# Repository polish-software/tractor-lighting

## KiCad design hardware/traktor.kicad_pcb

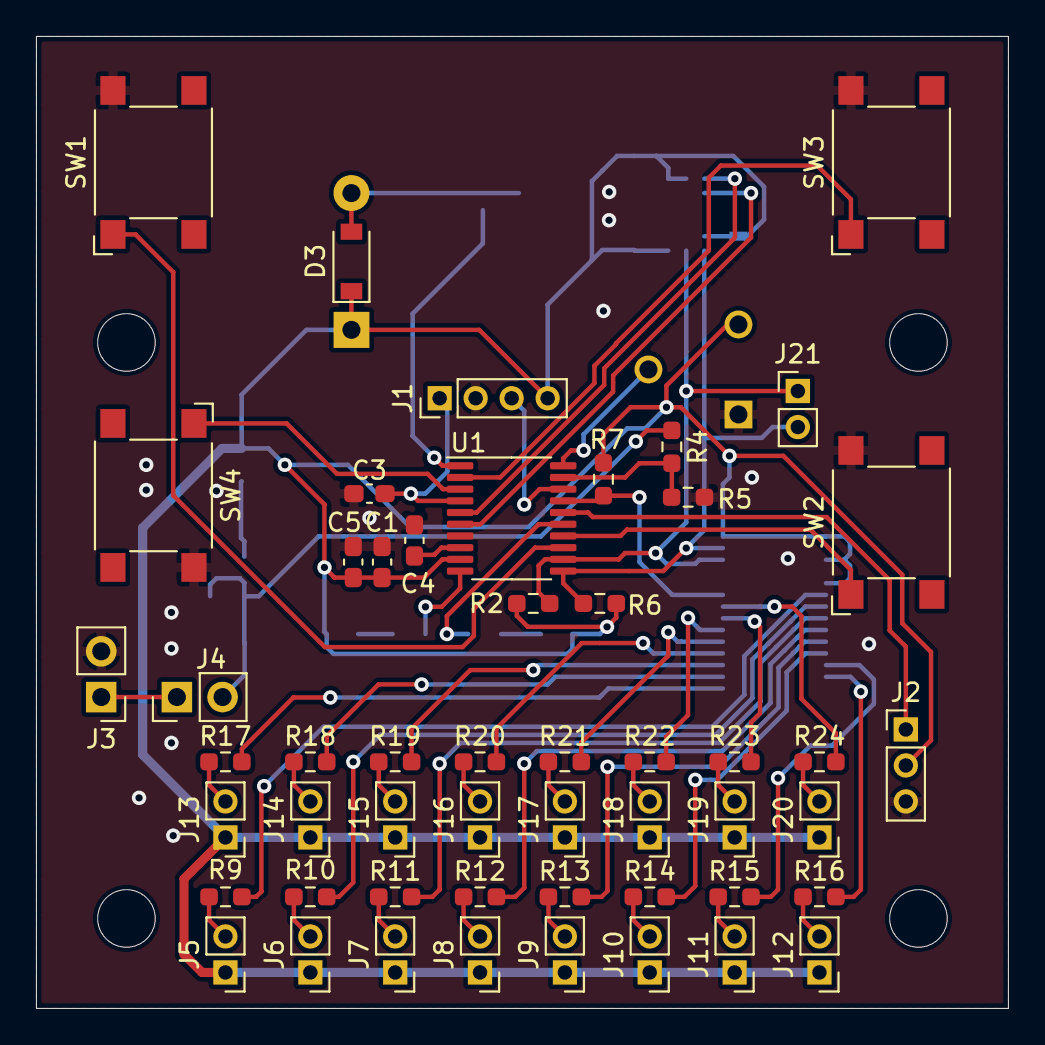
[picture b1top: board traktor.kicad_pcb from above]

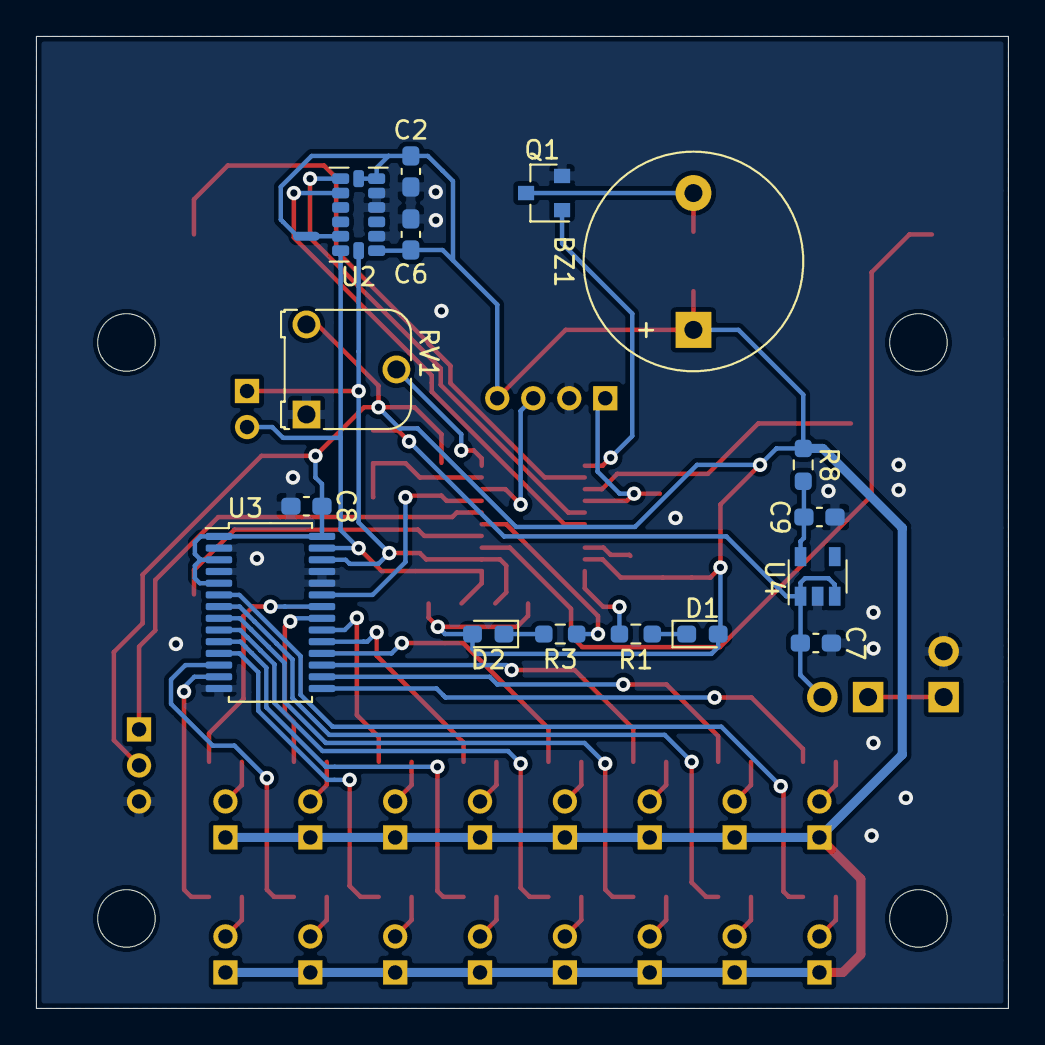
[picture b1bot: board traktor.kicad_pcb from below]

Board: 2 copper layers, 54.0 x 54.0 mm, 69 parts (17 on the bottom side), 59 nets.

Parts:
BZ1: Buzzer; Buzzer_12x9.5RM7.6
C1, C3, C8: 100nF; C_0603_1608Metric_Pad1.08x0.95mm_HandSolder
C2, C4, C5, C6, C7, C9: 1uF; C_0603_1608Metric_Pad1.08x0.95mm_HandSolder
D1, D2: LED; LED_0603_1608Metric_Pad1.05x0.95mm_HandSolder
D3: 1N4148W; D_SOD-123
J1: Conn_01x04_Male; PinHeader_1x04_P2.00mm_Vertical
J2: Conn_01x03_Male; PinHeader_1x03_P2.00mm_Vertical
J3, J4: Conn_01x02_Male; PinHeader_1x02_P2.54mm_Vertical
J5, J6, J7, J8, J9, J10, J11, J12, J13, J14, J15, J16, J17, J18, J19, J20, J21: Conn_01x02_Male; PinHeader_1x02_P2.00mm_Vertical
NT1: Net-Tie_2; NetTie-2_SMD_Pad0.5mm
Q1: BSS138; SOT-23
R1, R3: 1k; R_0603_1608Metric_Pad0.98x0.95mm_HandSolder
R2, R6: 4k7; R_0603_1608Metric_Pad0.98x0.95mm_HandSolder
R4: 47k; R_0603_1608Metric_Pad0.98x0.95mm_HandSolder
R5: 100k; R_0603_1608Metric_Pad0.98x0.95mm_HandSolder
R7: 10k; R_0603_1608Metric_Pad0.98x0.95mm_HandSolder
R8: 0R; R_0603_1608Metric_Pad0.98x0.95mm_HandSolder
R9, R10, R11, R12, R13, R14, R15, R16, R17, R18, R19, R20, R21, R22, R23, R24: 100R; R_0603_1608Metric_Pad0.98x0.95mm_HandSolder
RV1: R_POT; Potentiometer_Runtron_RM-065_Vertical
SW1, SW2, SW3, SW4: SW_Push; SW_SPST_Omron_B3FS-105xP
U1: STM8S003F3P; TSSOP-20_4.4x6.5mm_P0.65mm
U2: ADXL343; LGA-14_3x5mm_P0.8mm_LayoutBorder1x6y
U3: PCA9685PW; TSSOP-28_4.4x9.7mm_P0.65mm
U4: AP2112K-3.3; SOT-23-5

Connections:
+3V3: BZ1.1, C1.1, C2.1, C5.1, C6.1, C8.1, D1.2, D2.2, D3.1, J1.4, J2.2, J5.1, J6.1, J7.1, J8.1, J9.1, J10.1, J11.1, J12.1, J13.1, J14.1, J15.1, J16.1, J17.1, J18.1, J19.1, J20.1, NT1.1, R2.1, R6.1, R7.1, R8.1, RV1.3, U1.9, U2.1, U2.6, U2.7, U3.1, U3.3, U3.5, U3.28
+BATT: C7.1, J4.2, R4.1, U4.1, U4.3
/ACC_INT1: U1.5, U2.8
/ACC_INT2: U1.6, U2.9
/BAT_MEASURE: R4.2, R5.1, U1.19
/BUTTON1: SW1.1, U1.13
/BUTTON2: SW2.1, U1.14
/BUTTON3: SW3.1, U1.2
/BUTTON4: SW4.1, U1.3
/BUZZER: Q1.1, U1.1
/DBG_LED0: R1.2, U1.10
/DBG_LED1: R3.2, U1.15
/I2C_SCL: J21.1, R2.2, U1.12, U2.14, U3.26
/I2C_SDA: J21.2, R6.2, U1.11, U2.13, U3.27
/LED0: R9.2, U3.6
/LED1: R10.2, U3.7
/LED2: R11.2, U3.8
/LED3: R12.2, U3.9
/LED4: R13.2, U3.10
/LED5: R14.2, U3.11
/LED6: R15.2, U3.12
/LED7: R16.2, U3.13
/LED8: R17.2, U3.15
/LED9: R18.2, U3.16
/LED10: R19.2, U3.17
/LED11: R20.2, U3.18
/LED12: R21.2, U3.19
/LED13: R22.2, U3.20
/LED14: R23.2, U3.21
/LED15: R24.2, U3.22
/LEDS_ENABLE: R7.2, U1.17, U3.23
/POTENTIOMETER: RV1.2, U1.20
/RESET: C3.1, J1.1, U1.4
/SERVO: J2.1, U1.16
/SWIM: J1.3, U1.18
GND: C1.2, C2.2, C3.2, C4.2, C5.2, C6.2, C7.2, C8.2, C9.2, J1.2, J2.3, J3.2, Q1.2, R5.2, RV1.1, SW1.2, SW2.2, SW3.2, SW4.2, U1.7, U2.2, U2.4, U2.5, U3.2, U3.4, U3.14, U3.24, U3.25, U4.2
unnamed: BZ1.2, D3.2, Q1.3
unnamed: C4.1, U1.8
unnamed: C9.1, R8.2, U4.5
unnamed: D1.1, R1.1
unnamed: D2.1, R3.1
unnamed: J3.1, J4.1
unnamed: J5.2, R9.1
unnamed: J6.2, R10.1
unnamed: J7.2, R11.1
unnamed: J8.2, R12.1
unnamed: J9.2, R13.1
unnamed: J10.2, R14.1
unnamed: J11.2, R15.1
unnamed: J12.2, R16.1
unnamed: J13.2, R17.1
unnamed: J14.2, R18.1
unnamed: J15.2, R19.1
unnamed: J16.2, R20.1
unnamed: J17.2, R21.1
unnamed: J18.2, R22.1
unnamed: J19.2, R23.1
unnamed: J20.2, R24.1
unnamed: NT1.2, U2.12

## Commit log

2020-11-14 first commit - clocks initialization
2020-11-15 change Makefile - simpler procedure, add STM8S Standard Libraries to repo
2020-11-16 change Makefile - creating hex from .lib file, reduce hex file size
2020-11-17 add debug LEDs handling
2021-08-08 add I2C communication write bytes
2021-08-09 add PCB project
2021-08-10 add clang format
2021-08-10 add peripherals clocks control
2021-08-14 add LED PWM duty cycle setting
2021-08-14 add buttons pins configuration
2023-11-24 add buttons control
2023-11-24 add buttons to sources, fix makefile, remove binary from repo
2023-11-28 add buttons handling
2023-11-28 initialize ADC clock and GPIOs
